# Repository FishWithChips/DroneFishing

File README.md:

Drone Fishing

An open source repository for our Remote Control Drone Fishing Kit!

The Drone Fishing kit is a small battery powered device that you can connect to your drone.  
You then hook your fishing line from your fishing pole to the slider bar on the device.

Remotely connect to the device with wifi and then fly your drone out to the location you want to fish, 
Issue a single command and it will drop your bait into the water and your fishing.

Fly your drone home, or fly higher to watch your bait.  Don't scare away the fish!

Reel in your pole like normal, due to your extended cast you sure to catch a fish!
Just be careful and dont get your line tangled up somewhere!

We outline all the parts you need to put together your own drone fishing device!
Or you can buy our kit and assemble it yourself or order a fully assembled kit.

This is Fishing Awesome!

http://PowerBobber.com
http://DIYDroneFishing.com 

#DroneFishing

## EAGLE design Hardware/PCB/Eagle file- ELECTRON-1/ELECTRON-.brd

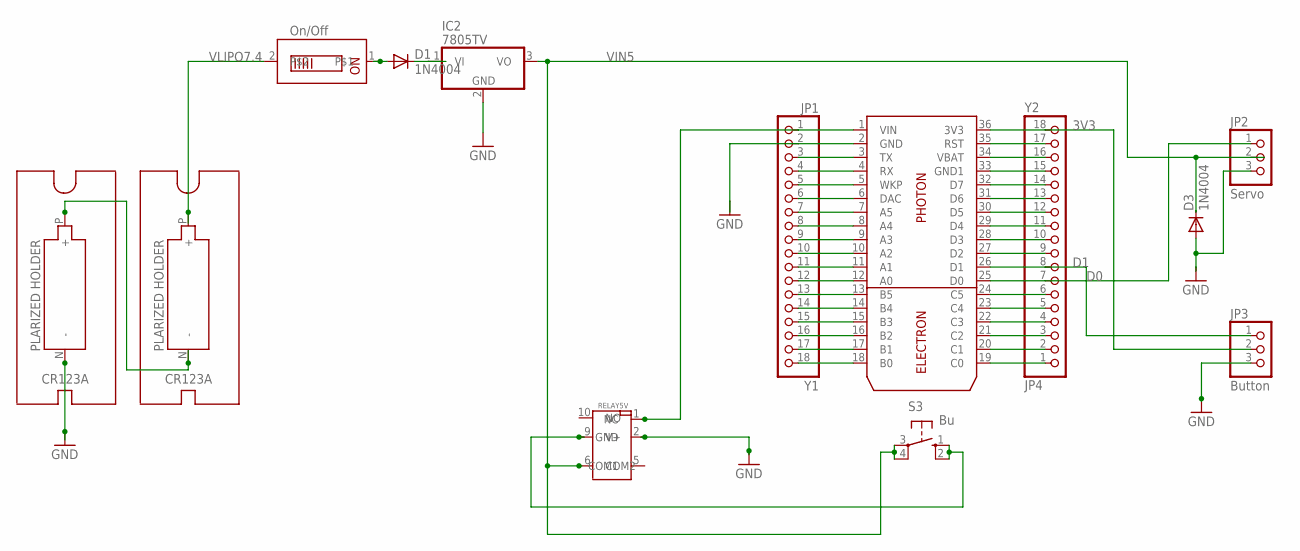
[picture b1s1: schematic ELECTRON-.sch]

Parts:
D1, D3: 1N4004; DO41-10
ELECTRON2: ELECTRON; ELECTRON-U260
IC2: 7805TV; TO220V
JP1: Y1; 1X18
JP2: Servo; 1X03/90
JP3: Button; 1X03/90
JP4: Y2; 1X18
S3: Bu; B3F-10XX
U$1, U$2: POLARIZEDHOLDER-CR123A; CRT123A
U$3: SWIDGET; GF-123-0054
U$4: RELAY5V; RELAY5V-F

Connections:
3V3: ELECTRON2.36 (3V3), JP3.2, JP4.18
D0: ELECTRON2.25 (D0), JP2.1, JP4.7
D1: ELECTRON2.26 (D1), JP3.1, JP4.8
GND: D3.A, ELECTRON2.2 (GND), IC2.2 (GND), JP1.2, JP2.3, JP3.3, U$1.N (-), U$4.2 (GND)
unnamed: S3.1 (S), S3.2 (S1), U$4.9 (V+)
unnamed: ELECTRON2.3 (TX), JP1.3
unnamed: D1.C, IC2.1 (VI)
unnamed: ELECTRON2.4 (RX), JP1.4
unnamed: ELECTRON2.33 (GND1), JP4.15
unnamed: ELECTRON2.5 (WKP), JP1.5
unnamed: U$1.P (+), U$2.N (-)
unnamed: ELECTRON2.6 (DAC), JP1.6
unnamed: ELECTRON2.35 (RST), JP4.17
unnamed: ELECTRON2.7 (A5), JP1.7
unnamed: ELECTRON2.34 (VBAT), JP4.16
unnamed: ELECTRON2.8 (A4), JP1.8
unnamed: ELECTRON2.9 (A3), JP1.9
unnamed: ELECTRON2.10 (A2), JP1.10
unnamed: ELECTRON2.32 (D7), JP4.14
unnamed: ELECTRON2.11 (A1), JP1.11
unnamed: ELECTRON2.31 (D6), JP4.13
unnamed: ELECTRON2.12 (A0), JP1.12
unnamed: ELECTRON2.13 (B5), JP1.13
unnamed: ELECTRON2.14 (B4), JP1.14
unnamed: ELECTRON2.15 (B3), JP1.15
unnamed: ELECTRON2.16 (B2), JP1.16
unnamed: ELECTRON2.17 (B1), JP1.17
unnamed: ELECTRON2.18 (B0), JP1.18
unnamed: ELECTRON2.30 (D5), JP4.12
unnamed: ELECTRON2.29 (D4), JP4.11
unnamed: ELECTRON2.28 (D3), JP4.10
unnamed: ELECTRON2.27 (D2), JP4.9
unnamed: ELECTRON2.24 (C5), JP4.6
unnamed: ELECTRON2.23 (C4), JP4.5
unnamed: ELECTRON2.22 (C3), JP4.4
unnamed: ELECTRON2.21 (C2), JP4.3
unnamed: ELECTRON2.20 (C1), JP4.2
unnamed: ELECTRON2.19 (C0), JP4.1
unnamed: D1.A, U$3.1
VIN5: D3.C, IC2.3 (VO), JP2.2, S3.3, S3.4 (P1), U$4.6 (COM2)
VLIPO7.4: U$2.P (+), U$3.2
VO5: ELECTRON2.1 (VIN), JP1.1, U$4.1 (NC)

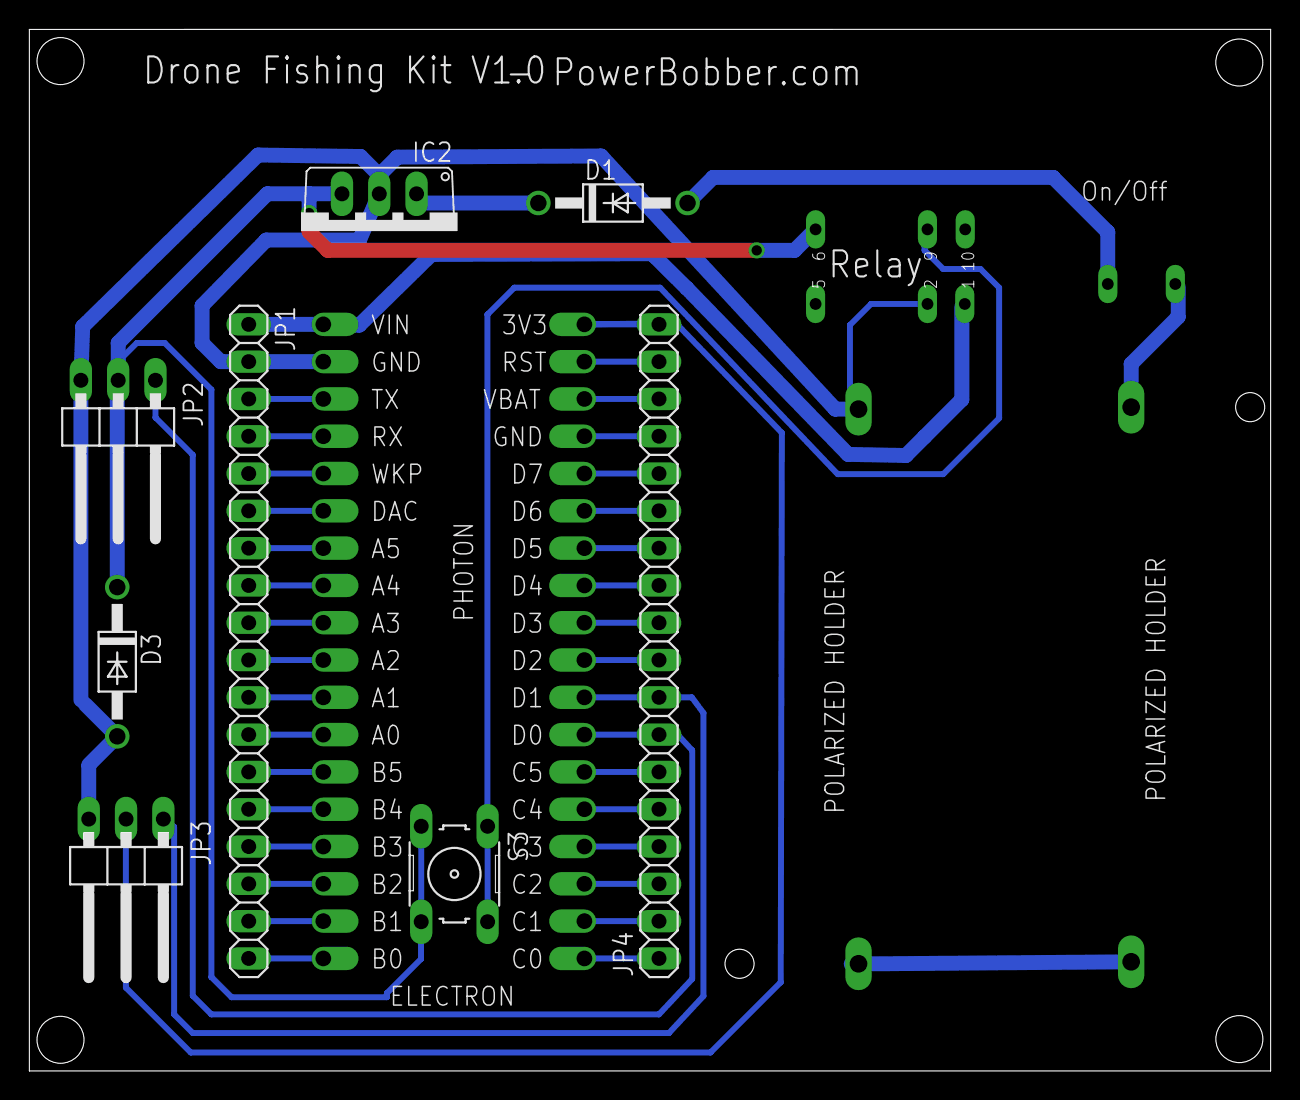
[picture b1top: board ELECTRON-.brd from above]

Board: 2 copper layers, 84.5 x 70.9 mm, 13 parts (0 on the bottom side), 42 nets.

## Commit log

2016-06-28 Adding initial version of The DIY Drone Fishing Kit (DFK). This software accompanies the DFK hardware which the current version runs on a Particle Photon powered device. Get more info at http://power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
2016-06-28 Updated Readme file with more information
2016-06-28 I didnt like the way Github displayed the page, updated format
2016-06-28 format update
2016-08-08 Initial draft on Xamarin app for Drone fishing
2016-08-23 Adding Xamarin Files
2016-08-23 renamed folders
2016-08-23 Adding .APK files
2016-08-23 Adding PCB files
2016-09-06 Added Servo Start and End position to UI
